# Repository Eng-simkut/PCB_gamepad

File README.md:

# PCB_gamepad
IN this projec i take on my first fully desighned PCB project in a quest to build my skills and improve my knowledge in PCB design. I start off by following an already designed project from you tube.  This is to help me remember how to get around KiCAD. I'm designing a gamepad.

Above is the PCB footprint of the Gamepad
Balow is its 3d views on both sides of the board

Below is its schematic

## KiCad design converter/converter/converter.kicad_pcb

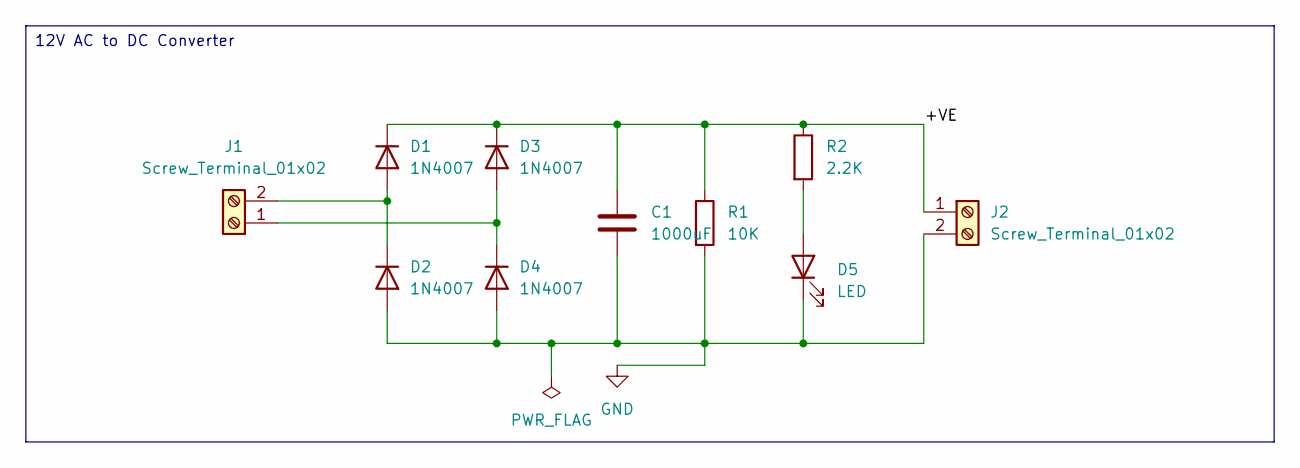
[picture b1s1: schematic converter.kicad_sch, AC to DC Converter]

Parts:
C1: 1000uF; C_Radial_D8.0mm_H11.5mm_P3.50mm
D1, D2, D3, D4: 1N4007; D_DO-41_SOD81_P10.16mm_Horizontal
D5: LED; LED_D5.0mm
J1, J2: Screw_Terminal_01x02; TerminalBlock_CUI_TB007-508-02_1x02_P5.08mm_Horizontal
R1: 10K; R_Axial_DIN0207_L6.3mm_D2.5mm_P7.62mm_Horizontal
R2: 2.2K; R_Axial_DIN0207_L6.3mm_D2.5mm_P7.62mm_Horizontal

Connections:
/+VE: C1.1, D1.1 (K), D3.1 (K), J2.1, R1.1, R2.1
GND: C1.2, D2.2 (A), D4.2 (A), D5.1 (K), J2.2, R1.2
unnamed: D1.2 (A), D2.1 (K), J1.2
unnamed: D3.2 (A), D4.1 (K), J1.1
unnamed: D5.2 (A), R2.2

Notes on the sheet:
12V AC to DC Converter

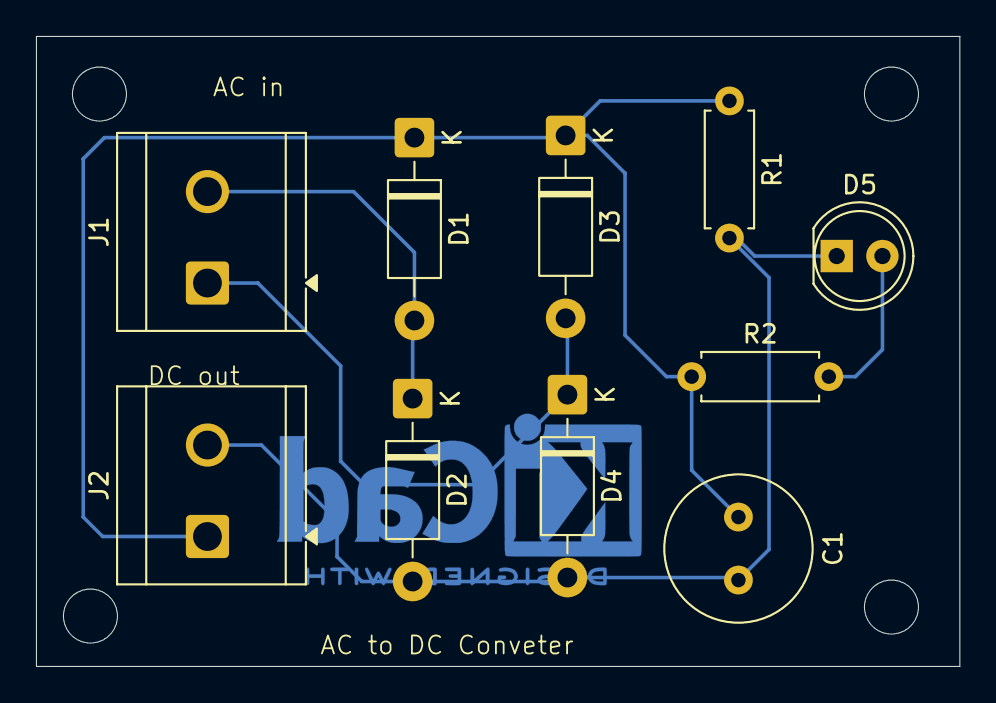
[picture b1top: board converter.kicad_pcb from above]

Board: 2 copper layers, 51.3 x 35.0 mm, 10 parts (0 on the bottom side), 5 nets.

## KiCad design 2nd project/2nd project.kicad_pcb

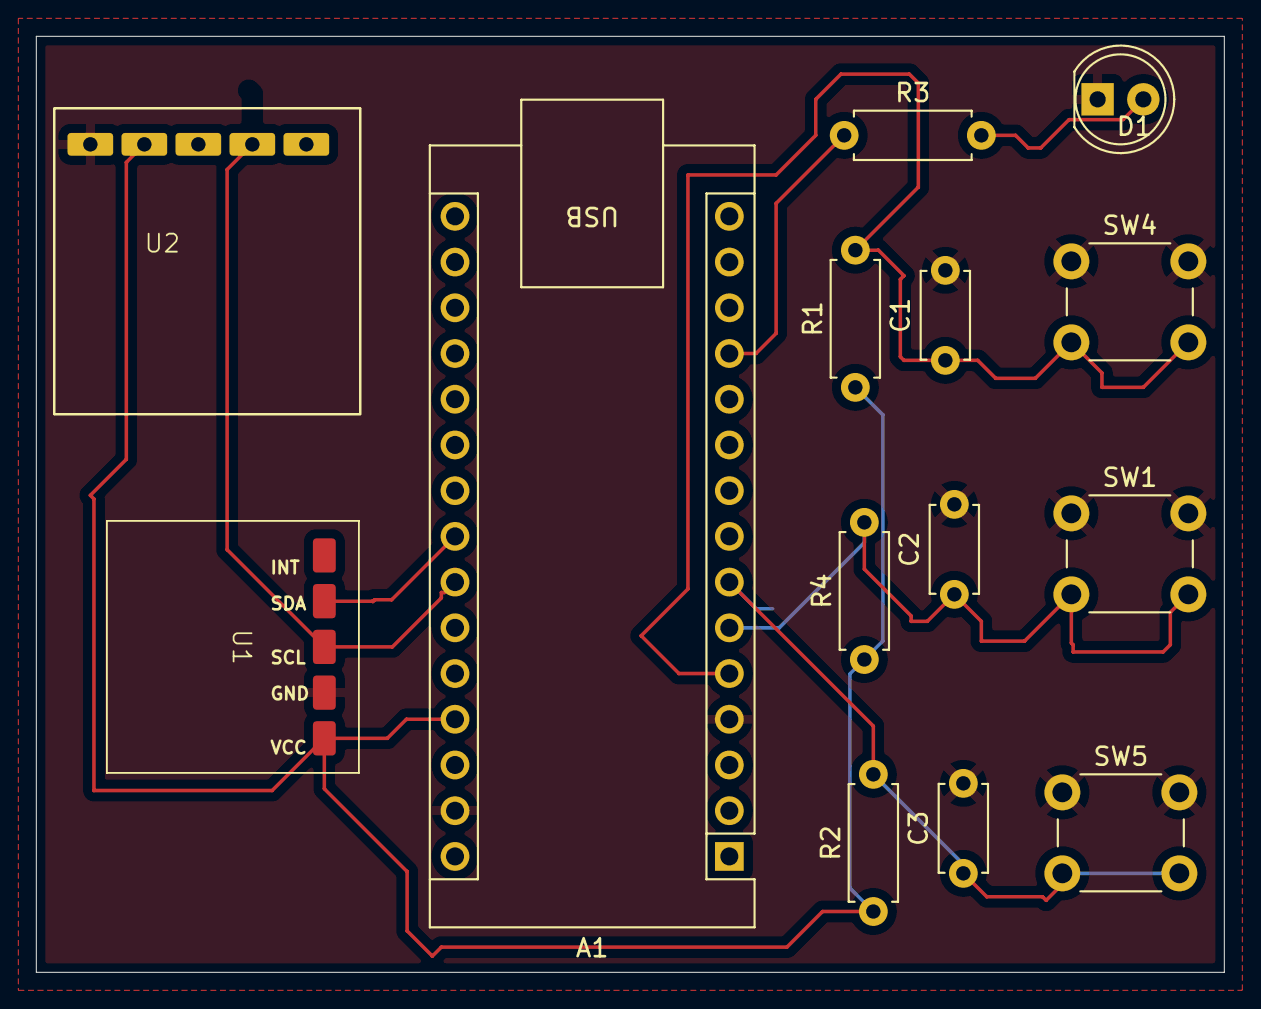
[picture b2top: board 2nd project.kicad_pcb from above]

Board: 4 copper layers, 66.0 x 52.0 mm, 14 parts (0 on the bottom side), 9 nets.

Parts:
A1: Arduino_Nano_v3.x; Arduino_Nano
C1, C2, C3: C; C_Disc_D4.7mm_W2.5mm_P5.00mm
D1: LED; LED_D5.0mm
R1, R4: 1k; R_Axial_DIN0207_L6.3mm_D2.5mm_P7.62mm_Horizontal
R2, R3: 1K; R_Axial_DIN0207_L6.3mm_D2.5mm_P7.62mm_Horizontal
SW1, SW4, SW5: SW_Push; SW_PUSH_6mm
U1: MAX30102
U2: SSD1306

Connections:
+5V: A1.27 (+5V), R1.1, R2.1, R4.1, U1.5 (VCC), U2.2 (VCC)
GND: A1.4 (GND), A1.29 (GND), C1.2, C2.2, C3.2, D1.1 (K), SW1.1, SW4.1, SW5.1, U1.4 (GND), U2.1 (GND)
unnamed: A1.23 (A4), U1.2 (SDA)
unnamed: A1.24 (A5), U1.3 (SCL), U2.4 (SCL)
unnamed: A1.5 (D2), C1.1, R1.2, SW4.2
unnamed: A1.6 (D3), C2.1, R4.2, SW1.2
unnamed: A1.7 (D4), C3.1, R2.2, SW5.2
unnamed: A1.12 (D9), R3.1
unnamed: D1.2 (A), R3.2

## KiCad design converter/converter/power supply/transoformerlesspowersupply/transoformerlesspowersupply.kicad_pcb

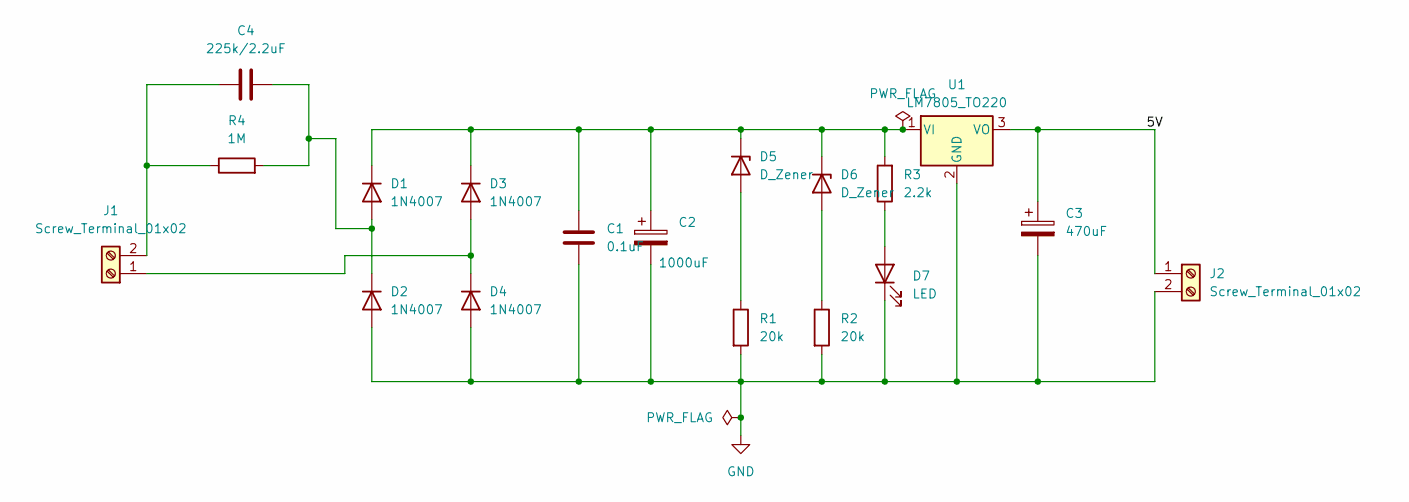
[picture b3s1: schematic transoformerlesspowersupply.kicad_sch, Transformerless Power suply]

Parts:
C1: 0.1uF; C_Disc_D4.7mm_W2.5mm_P5.00mm
C2: 1000uF; CP_Radial_D10.0mm_P5.00mm
C3: 470uF; CP_Radial_D10.0mm_P3.80mm
C4: 225k/2.2uF; C_Rect_L18.0mm_W6.0mm_P15.00mm_FKS3_FKP3
D1, D2, D3, D4: 1N4007; D_DO-41_SOD81_P10.16mm_Horizontal
D5, D6: D_Zener; D_A-405_P7.62mm_Horizontal
D7: LED; LED_D5.0mm
J1, J2: Screw_Terminal_01x02; TerminalBlock_MaiXu_MX126-5.0-02P_1x02_P5.00mm
R1, R2: 20k; R_Axial_DIN0207_L6.3mm_D2.5mm_P7.62mm_Horizontal
R3: 2.2k; R_Axial_DIN0207_L6.3mm_D2.5mm_P7.62mm_Horizontal
R4: 1M; R_Axial_DIN0207_L6.3mm_D2.5mm_P7.62mm_Horizontal
U1: LM7805_TO220; TO-220-3_Vertical

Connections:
/5V: C3.1, J2.1, U1.3 (VO)
GND: C1.2, C2.2, C3.2, D2.2 (A), D4.2 (A), D7.1 (K), J2.2, R1.2, R2.2, U1.2 (GND)
unnamed: C4.2, D1.2 (A), D2.1 (K), R4.2
unnamed: C1.1, C2.1, D1.1 (K), D3.1 (K), D5.1 (K), D6.1 (K), R3.2, U1.1 (VI)
unnamed: D3.2 (A), D4.1 (K), J1.1
unnamed: D5.2 (A), R1.1
unnamed: D6.2 (A), R2.1
unnamed: D7.2 (A), R3.1
unnamed: C4.1, J1.2, R4.1

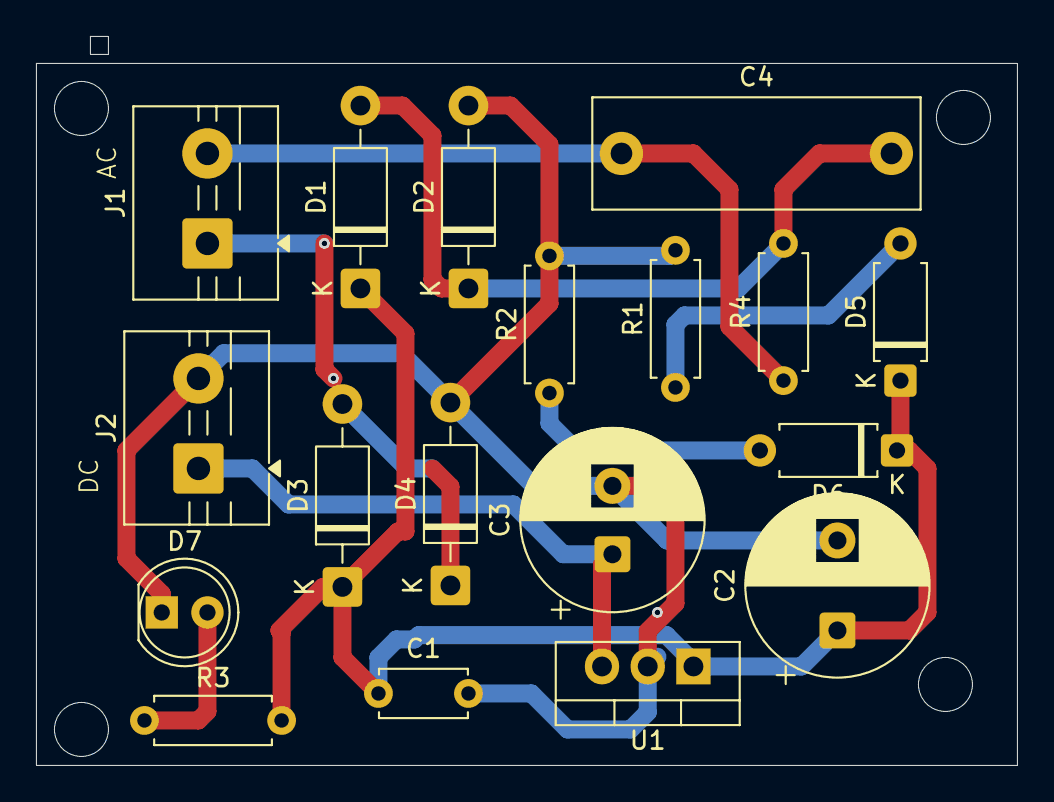
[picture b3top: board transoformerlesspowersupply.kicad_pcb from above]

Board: 2 copper layers, 54.5 x 40.5 mm, 18 parts (0 on the bottom side), 9 nets.

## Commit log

2026-05-02 Intitial commit:Added gamepad schematic and project files
2026-05-08 Fix typos and improve README content
    Correct spelling and grammar in project description.
